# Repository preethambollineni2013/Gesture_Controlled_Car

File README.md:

# Gesture Controlled Car

A car that can be controlled using hand movements. By tilting my wrist, I can control the direction and speed of the car without using a traditional remote controller.

The project uses a motion sensor mounted on a hand-worn transmitter. The transmitter sends the movement data wirelessly to the car, where a microcontroller controls the motors.

---

## How It Works

The project has two main parts:

### 1. Transmitter (Hand Unit)

The transmitter consists of an ESP32 and a BNO055 motion sensor. The sensor detects the tilt of the hand and the ESP32 processes the movement data. It then sends the commands to the car through Wi-Fi.

### 2. Receiver (Car Unit)

The receiver uses an Arduino UNO R4 WiFi and a motor driver. It receives the commands from the transmitter and controls the four DC motors according to the hand movement.

---

## Hand Movement Controls

| Hand Movement | Car Action |
|---|---|
| Tilt wrist forward | Move forward |
| Tilt wrist backward | Move backward |
| Tilt wrist right | Turn right |
| Tilt wrist left | Turn left |
| Keep hand level | Stop |

---

## Main Components

### Transmitter

- ESP32 DevKitC-32E
- BNO055 motion sensor
- 3.7V 2000mAh Li-Po battery
- TP4056 USB-C charging module
- 5V boost converter
- Slide switch
- 100µF capacitor

### Receiver

- Arduino UNO R4 WiFi
- Cytron MDD10A motor driver
- 4 yellow TT gear motors
- 4 wheels (65mm)
- 2 × 18650 batteries
- 2S battery protection board
- 10A fuse
- XT60 connector
- Power switch

---

## Communication

The transmitter creates its own Wi-Fi network named **"GestureCar"**. The car connects to this network and receives movement information through UDP communication.

The transmitter sends data at 50 packets per second. The receiver uses the received throttle and steering values to control the left and right motors.

The system also includes a safety feature that stops the motors when communication is interrupted.

---

## PCB Design

Two separate PCBs are designed for the project.

| Feature | Transmitter PCB | Receiver PCB |
|---|---|---|
| Size | 92 × 64 mm | 116 × 64 mm |
| Layers | 2 | 2 |
| Thickness | 1.6 mm | 1.6 mm |
| Main controller | ESP32 | Arduino UNO R4 WiFi |

The transmitter PCB contains the connections for the ESP32, motion sensor and power supply modules.

The receiver PCB provides the connections for the Arduino, motor driver signals and battery supply.

Both PCB designs include mounting holes and connectors for easier assembly.

---

## 3D Chassis Design

The car body is designed as a separate base and lid. The design also includes four motor brackets.

The main parts are:

- Car body base
- Top lid
- Two types of motor brackets
- Mounting positions for the receiver PCB
- Space for the battery and motor driver

The chassis is designed for orange PETG 3D printing. The motor brackets hold the four TT gear motors in position.

### 3D Model Files

| File | Description |
|---|---|
| `car_body_base.stl` | Main chassis |
| `car_lid.stl` | Top cover |
| `motor_bracket_A.stl` | Motor mounting bracket |
| `motor_bracket_B.stl` | Mirrored motor mounting bracket |

---

## Software

The project uses Arduino IDE to program both controllers.

### Transmitter code: `gesture_transmitter.ino`

- Reads the BNO055 sensor.
- Detects hand tilt.
- Calculates throttle and steering values.
- Sends data wirelessly through UDP.

### Receiver code: `gesture_receiver.ino`

- Receives data from the transmitter.
- Processes movement commands.
- Controls the motor driver.
- Adjusts motor speed and direction.
- Stops the motors when the wireless connection is lost.

Both programs include adjustable settings for sensor direction, motor direction, speed and movement sensitivity.

---

## Project Files

```text
Gesture_Controlled_Car/
│
├── README.md
├── JOURNAL.md
├── BOM.md
├── LICENSE
│
├── gesture_transmitter.ino
├── gesture_receiver.ino
│
├── gesture_tx_gerbers.zip
├── gesture_rx_gerbers.zip
│
├── car_body_base.stl
├── car_lid.stl
├── motor_bracket_A.stl
└── motor_bracket_B.stl
```

---

## Power Supply

The transmitter uses a 3.7V Li-Po battery with a charging module and a 5V boost converter.

The car uses two 18650 cells connected in series with a suitable battery protection board. The motor power is controlled through the Cytron MDD10A driver.

The motor speed is limited in the program to suit the selected motors.

---

## Safety Notes

- Use a suitable battery protection circuit.
- Check the polarity before connecting the power supply.
- Use the correct charger for the battery configuration.
- Keep the motor wheels clear of the ground when checking motor operation.
- Avoid short circuits in the battery connections.

---

## Bill of Materials

The complete component list, quantities and estimated prices are available in [BOM.md](BOM.md).

---

## Project Journal

The development process, including planning, component selection, circuit diagrams, PCB design, chassis modelling, programming and documentation, is recorded in [JOURNAL.md](JOURNAL.md).

---

## License

This project is licensed under the MIT License. See the [LICENSE](LICENSE) file for details.

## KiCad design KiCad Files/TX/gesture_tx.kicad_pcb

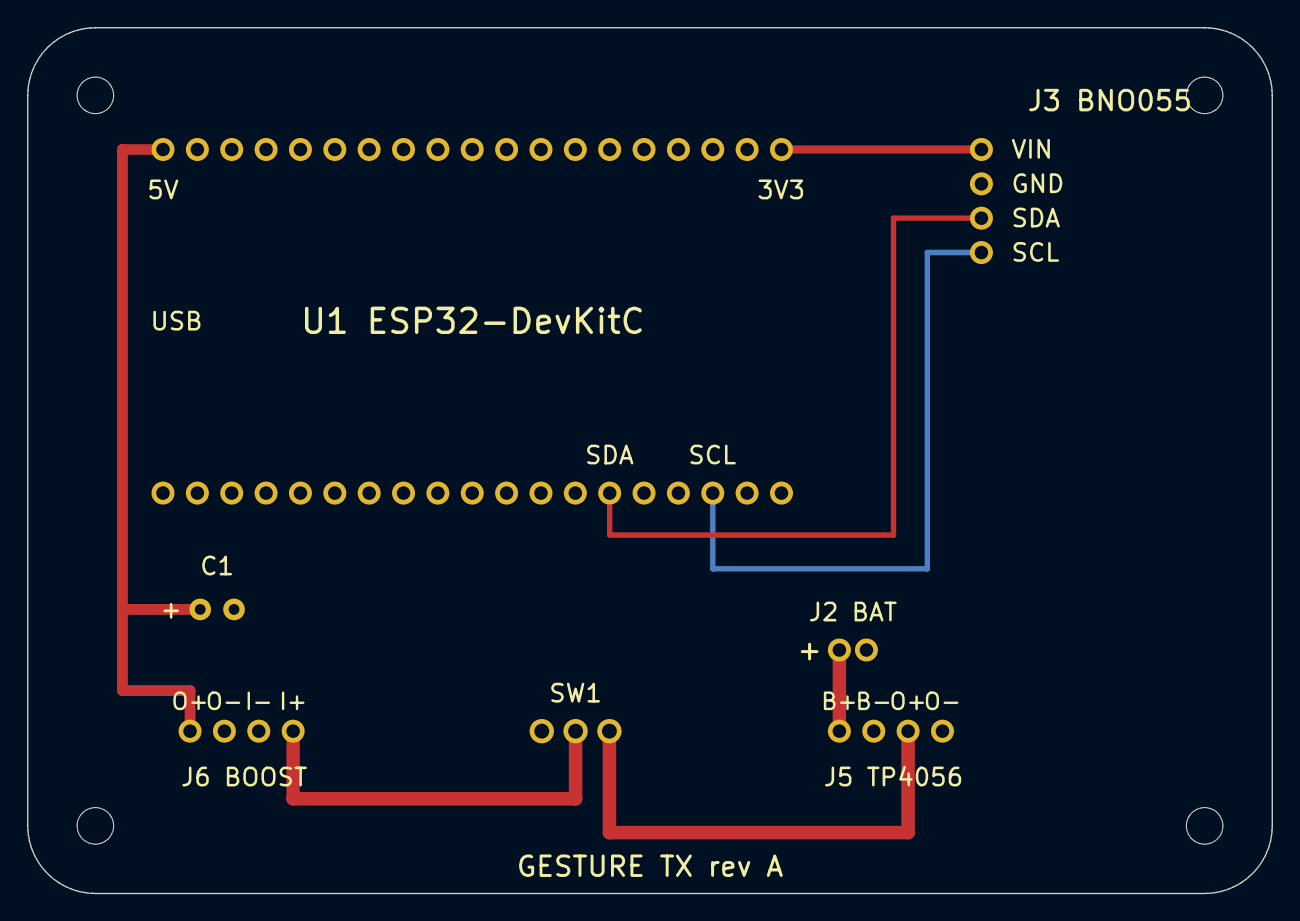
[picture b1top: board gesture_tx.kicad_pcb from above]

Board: 2 copper layers, 92.0 x 64.0 mm, 11 parts (0 on the bottom side), 8 nets.

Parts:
C1: CP_Radial_D6.3mm_P2.50mm
H1, H2, H3, H4: MountingHole_2.7mm
J2: JST_PH_S2B-PH-K
J3, J5, J6: PinHeader_1x04_P2.54mm
SW1: SlideSwitch_3pin_P2.5mm
U1: ESP32_DevKitC_Sockets

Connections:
3V3: J3.1, U1.19
5V: C1.1, J6.1, U1.1
BATT: J2.1, J5.1
CHGOUT: J5.3, SW1.3
GND: C1.2, J2.2, J3.2, J5.2, J5.4, J6.2, J6.3, U1.6, U1.32, U1.38
SCL: J3.4, U1.36
SDA: J3.3, U1.33
SWOUT: J6.4, SW1.2

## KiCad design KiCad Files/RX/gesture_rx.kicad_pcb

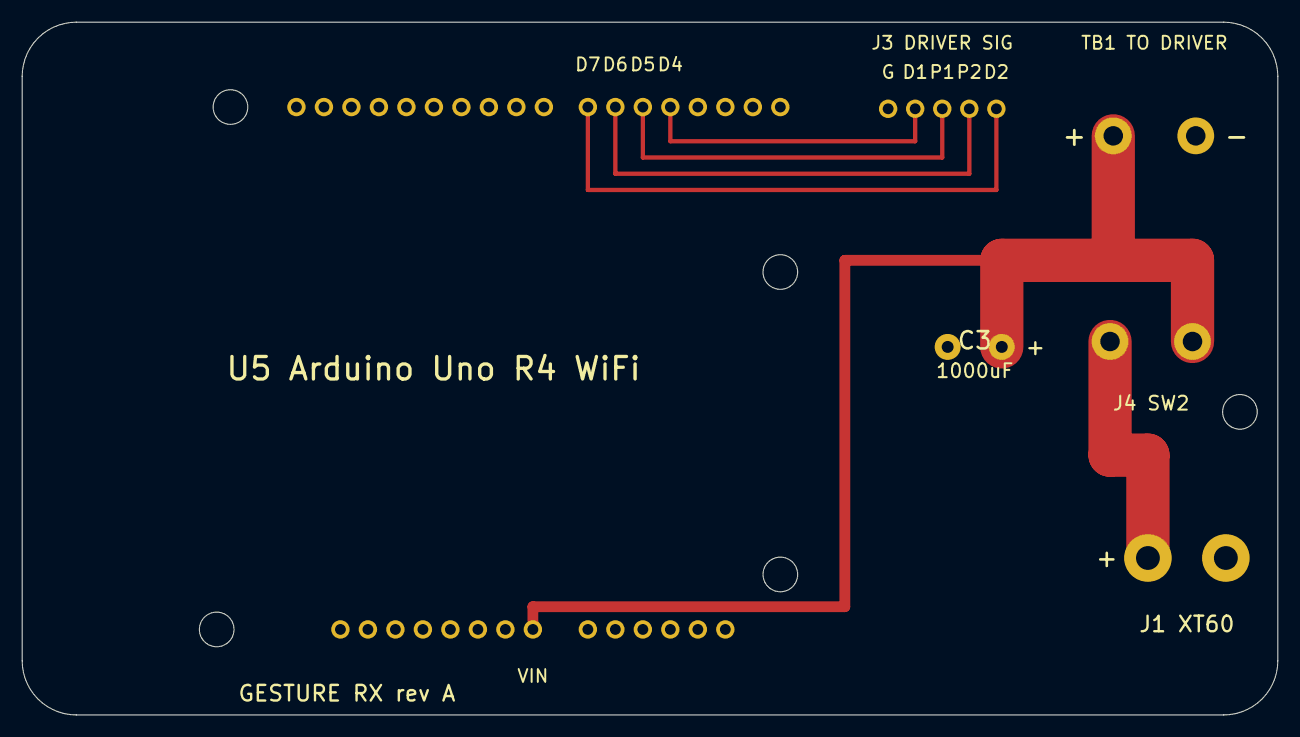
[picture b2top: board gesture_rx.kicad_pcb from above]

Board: 2 copper layers, 116.0 x 64.0 mm, 11 parts (0 on the bottom side), 7 nets.

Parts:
C3: CP_Radial_D10mm_P5.00mm
H1, H2, H3, H4, H5: MountingHole_3.2mm
J1: XT60PW
J3: JST_XH_B5B-XH-A
J4: TerminalBlock_P7.62mm_2pin
TB1: TerminalBlock_P7.62mm_2pin
U5: Arduino_Uno_Shield_Sockets

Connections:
BATT: J1.1, J4.1
DIR1: J3.2, U5.14
DIR2: J3.5, U5.11
GND: C3.2, J1.2, J3.1, TB1.2, U5.4, U5.24, U5.25
PWM1: J3.3, U5.13
PWM2: J3.4, U5.12
VBAT: C3.1, J4.2, TB1.1, U5.26
